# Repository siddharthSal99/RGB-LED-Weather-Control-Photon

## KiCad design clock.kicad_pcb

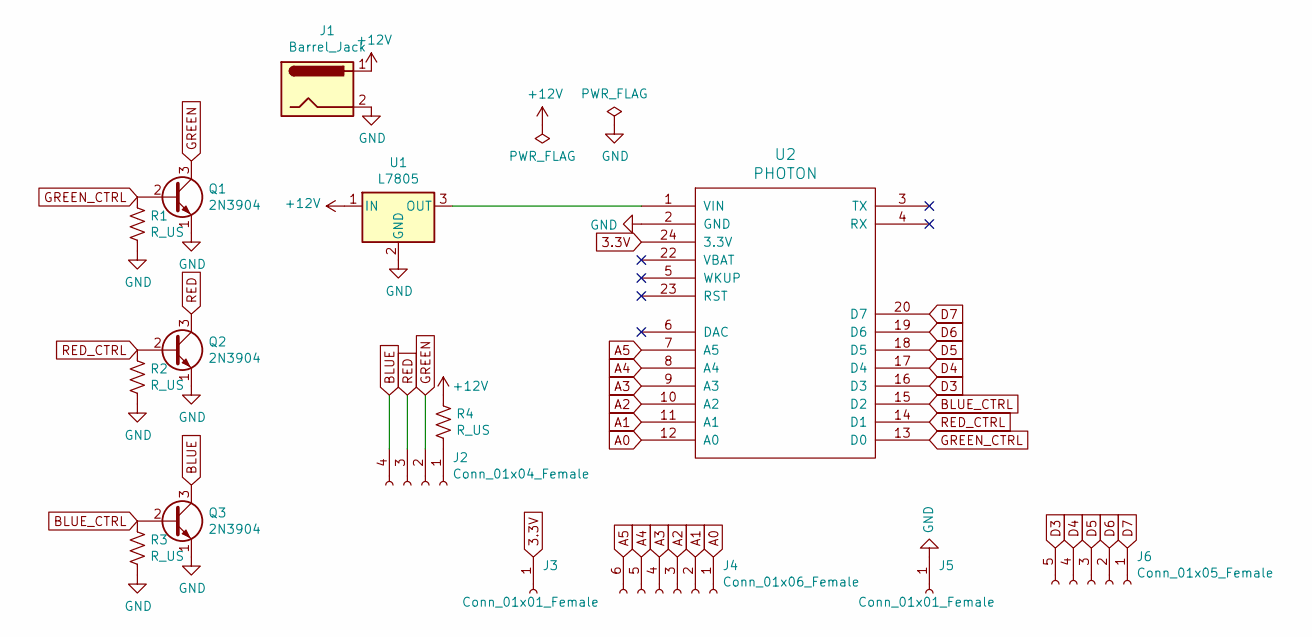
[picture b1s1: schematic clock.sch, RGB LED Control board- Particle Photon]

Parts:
J1: Barrel_Jack; BARREL_JACK
J2: Conn_01x04_Female; Pin_Header_Straight_1x04_Pitch2.54mm
J3, J5: Conn_01x01_Female; Pin_Header_Straight_1x01_Pitch2.54mm
J4: Conn_01x06_Female; Pin_Header_Straight_1x06_Pitch2.54mm
J6: Conn_01x05_Female; Pin_Header_Straight_1x05_Pitch2.54mm
Q1, Q2, Q3: 2N3904; TO-92_Inline_Narrow_Oval
R1, R2, R3, R4: R_US; R_Axial_DIN0204_L3.6mm_D1.6mm_P1.90mm_Vertical
U1: L7805; Pin_Header_Straight_1x03_Pitch2.54mm
U2: PHOTON

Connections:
3.3V: J3.1, U2.24 (3.3V)
+12V: J1.1, R4.1, U1.1 (IN)
A0: J4.1, U2.12 (A0)
A1: J4.2, U2.11 (A1)
A2: J4.3, U2.10 (A2)
A3: J4.4, U2.9 (A3)
A4: J4.5, U2.8 (A4)
A5: J4.6, U2.7 (A5)
BLUE: J2.4, Q3.3 (C)
BLUE_CTRL: Q3.2 (B), R3.1, U2.15 (D2)
D3: J6.5, U2.16 (D3)
D4: J6.4, U2.17 (D4)
D5: J6.3, U2.18 (D5)
D6: J6.2, U2.19 (D6)
D7: J6.1, U2.20 (D7)
GND: J1.2, J5.1, Q1.1 (E), Q2.1 (E), Q3.1 (E), R1.2, R2.2, R3.2, U1.2 (GND), U2.2 (GND)
GREEN: J2.2, Q1.3 (C)
GREEN_CTRL: Q1.2 (B), R1.1, U2.13 (D0)
unnamed: J2.1, R4.2
unnamed: U1.3 (OUT), U2.1 (VIN)
RED: J2.3, Q2.3 (C)
RED_CTRL: Q2.2 (B), R2.1, U2.14 (D1)

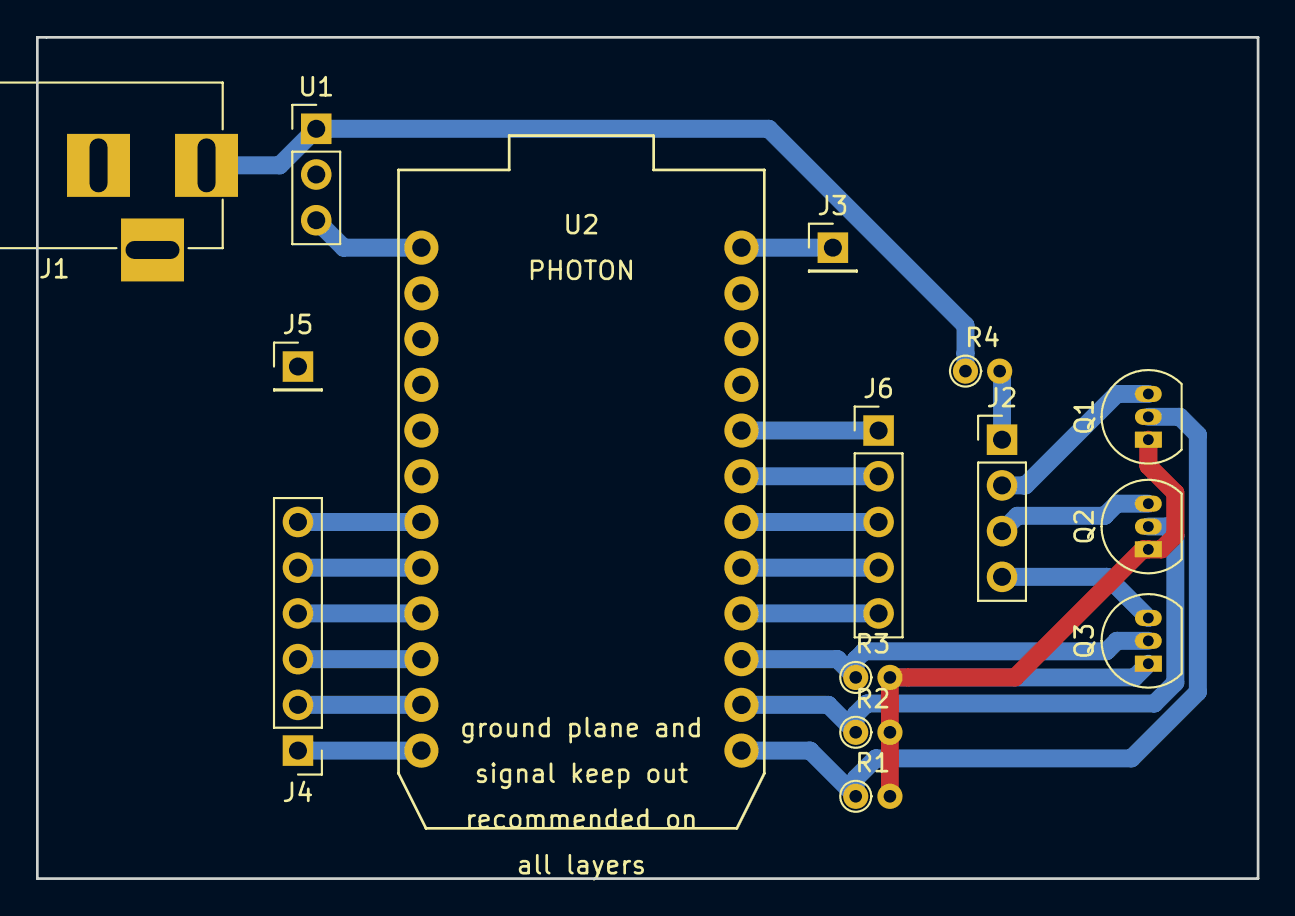
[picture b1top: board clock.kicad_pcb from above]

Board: 2 copper layers, 67.8 x 46.7 mm, 15 parts (0 on the bottom side), 22 nets.
